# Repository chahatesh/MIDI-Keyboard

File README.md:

# MIDI Keyboard

This is a custom-built MIDI keyboard that I designed using a PCB and electronic components. The goal of this project was to create a compact, customizable MIDI controller with different types of inputs, including capacitive touch keys, buttons, sliders, and rotary encoders.

The keyboard is designed to be assembled by soldering components onto a custom PCB and uploading the firmware to the microcontroller.

All the PCB design files are included in this repository so you can build your own!

## Images

## Features

The MIDI keyboard includes several different controls:

- **Capacitive Touch Keys** – Touch-sensitive keys that can be used for musical notes or other inputs.
- **Push Buttons** – Additional buttons that can be programmed for different functions.
- **Sliders** – Adjustable controls for changing values such as volume or effects.
- **Rotary Encoders** – Rotating controls that can be used to adjust settings.
- **RGB LEDs** – SK6812MINI-E LEDs for visual feedback.
- **Custom PCB** – A board designed specifically for this project.

The firmware can be modified to change how the controls work, making the keyboard customizable for different applications.

## How to Build

### 1. Order the PCB

Start by downloading the PCB manufacturing files from this repository.

You can order the board from a PCB manufacturer such as [JLCPCB](https://jlcpcb.com/) or another PCB fabrication service.

Make sure to use the correct PCB files and check the board specifications before ordering.

### 2. Get the Components

Once you have ordered the PCB, you'll need to get all the electronic components required for the build.

These include the components shown in the PCB design, such as:

- Microcontroller and supporting components
- Buttons and switches
- Capacitive touch components
- Sliders
- Rotary encoders
- SK6812MINI-E LEDs
- Resistors, capacitors, and other components

Check the PCB design and bill of materials (BOM), if provided, for the exact parts and quantities.

### 3. Solder the Components

Once your PCB and components arrive, you can start assembling the keyboard.

Follow the PCB layout to determine where each component belongs.

I recommend starting with the smaller components before moving on to larger parts such as buttons, sliders, and rotary encoders.

Make sure that:

- Components are placed in the correct positions.
- Polarized components are facing the correct direction.
- Solder joints are clean and properly connected.
- There are no accidental solder bridges between pins.

Before connecting power, double-check the board for any mistakes.

### 4. Upload the Code

After soldering everything, connect the keyboard to your computer using the appropriate USB cable or programming connection.

Open the firmware in its supported development environment, select the correct board and port, and upload the code.

The firmware handles the keyboard's inputs and outputs, including its buttons, touch keys, sliders, encoders, and LEDs.

You can also modify the code to customize how the keyboard responds to different inputs.

### 5. Test Everything

After uploading the code, test the different parts of the keyboard.

Check that the buttons, touch keys, sliders, rotary encoders, and LEDs are responding correctly.

If something isn't working, check the solder joints, wiring, component orientation, and firmware settings.

If your firmware supports MIDI output, you can also connect the keyboard to compatible music software and test its MIDI controls.

### 6. Have Fun!

Once everything is working, your custom keyboard is ready!

You can experiment with different firmware, customize the controls, and use it for your own projects.

## CAD Design

The CAD model for this project is available on Onshape.

(https://cad.onshape.com/documents/587d2ace9f77041b4f50040f/w/845a50b27325c4e045b03186/e/2a77872a340160e4eacdba4f?renderMode=0&uiState=6ade809f7d59ddcf278d1ba7)

You can use this model to view the mechanical design, check dimensions, and understand how the parts fit together.

## Project Files

This repository contains the files needed to understand and reproduce the project.

- `Instrument/` – PCB design files, including the electronic design.
- `Images/` – Screenshots and images of the project.
- 'Code/' – Code used to control the keyboard, where included.

## Customization

One of the main reasons I made this keyboard was to have something that could be customized.

Depending on the firmware, you can experiment with different button functions, MIDI note mappings, slider controls, encoder behavior, and LED effects.

You can also modify the PCB design or CAD model to create your own version.

## About the Project

I created this project to learn more about PCB design, electronics, soldering, and programming.

It combines hardware and software into one device and provides a way to experiment with different input methods.

Feel free to explore the files, modify the design, and build your own version!

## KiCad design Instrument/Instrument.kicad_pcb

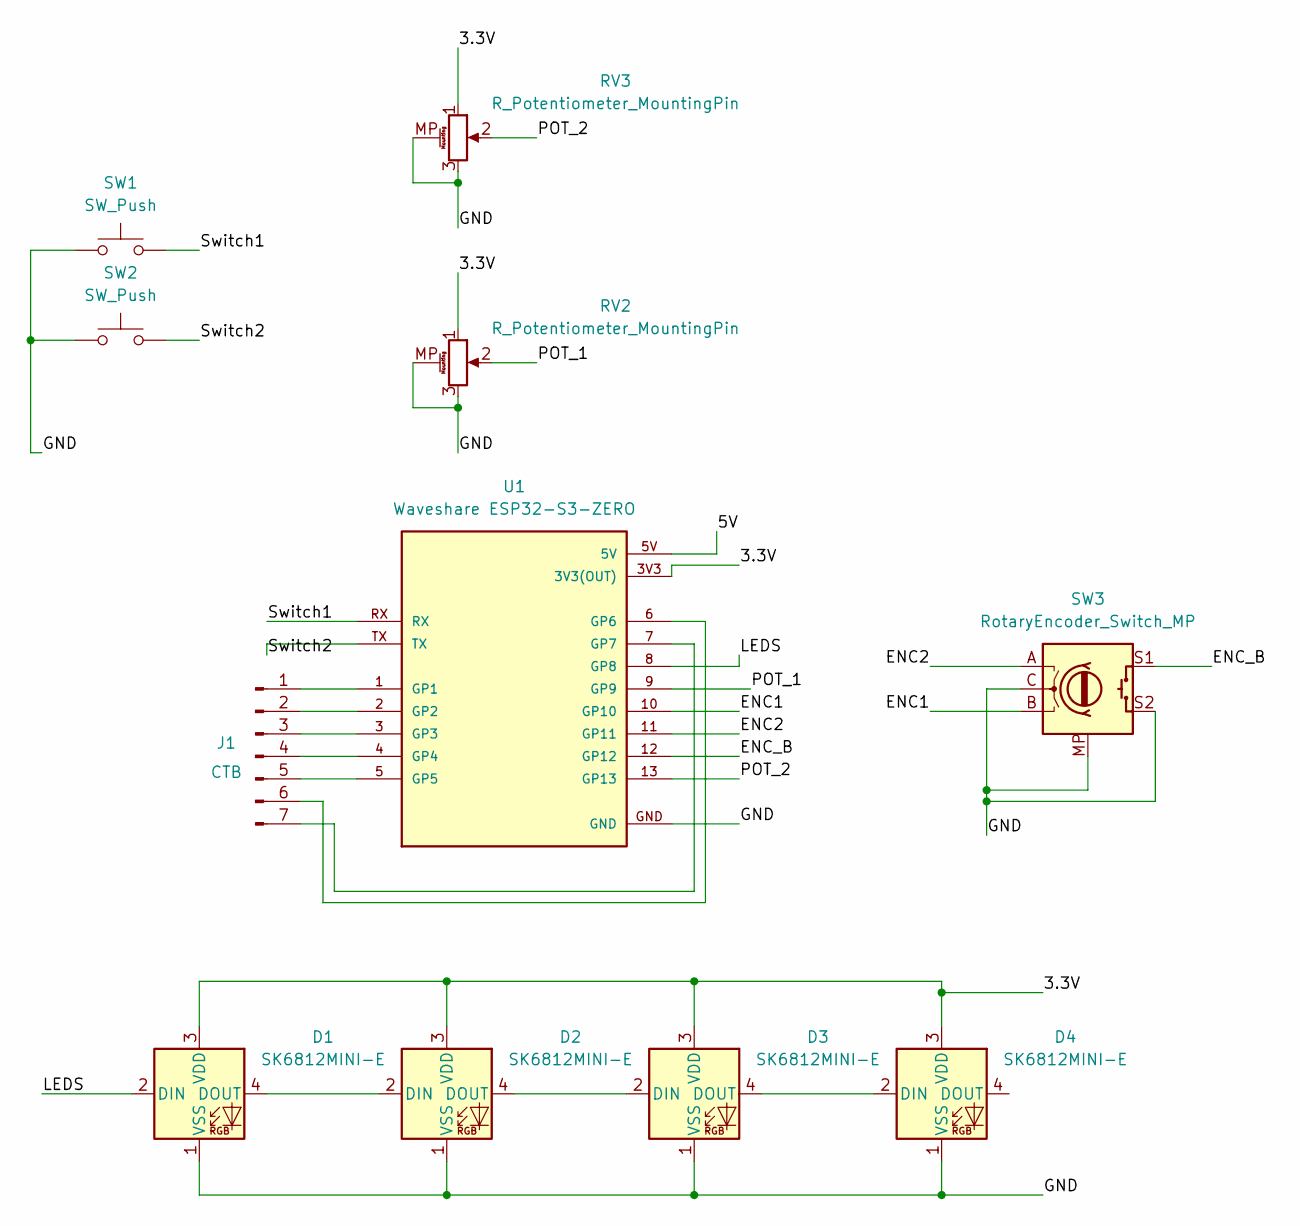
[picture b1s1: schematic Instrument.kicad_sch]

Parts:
D1, D2, D3, D4: SK6812MINI-E; LED_SK6812MINI-E_3.2x2.8mm_P1.5mm_ReverseMount
J1: CTB; Hex-Keys
RV2, RV3: R_Potentiometer_MountingPin; Potentiometer_Bourns_PTA1543_Single_Slide
SW1, SW2: SW_Push; Kailh Choc Low-Profile Switches
SW3: RotaryEncoder_Switch_MP; RotaryEncoder_Alps_EC11E-Switch_Vertical_H20mm_MountingHoles
U1: Waveshare ESP32-S3-ZERO; Waveshare ESP32-S3-Zero; PARTREV NA

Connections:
/3.3V: D1.3 (VDD), D2.3 (VDD), D3.3 (VDD), D4.3 (VDD), RV2.1, RV3.1, U1.3V3 (3V3(OUT))
/5V: U1.5V
/ENC1: SW3.B, U1.10 (GP10)
/ENC2: SW3.A, U1.11 (GP11)
/ENC_B: SW3.S1, U1.12 (GP12)
/GND: D1.1 (VSS), D2.1 (VSS), D3.1 (VSS), D4.1 (VSS), RV2.3, RV2.MP (MountPin), RV3.3, RV3.MP (MountPin), SW1.1, SW2.1, SW3.C, SW3.MP, SW3.S2, U1.GND
/LEDS: D1.2 (DIN), U1.8 (GP8)
/POT_1: RV2.2, U1.9 (GP9)
/POT_2: RV3.2, U1.13 (GP13)
/Switch1: SW1.2, U1.RX
/Switch2: SW2.2, U1.TX
unnamed: D1.4 (DOUT), D2.2 (DIN)
unnamed: D2.4 (DOUT), D3.2 (DIN)
unnamed: D3.4 (DOUT), D4.2 (DIN)
unnamed: J1.1, U1.1 (GP1)
unnamed: J1.2, U1.2 (GP2)
unnamed: J1.3, U1.3 (GP3)
unnamed: J1.4, U1.4 (GP4)
unnamed: J1.5, U1.5 (GP5)
unnamed: J1.6, U1.6 (GP6)
unnamed: J1.7, U1.7 (GP7)

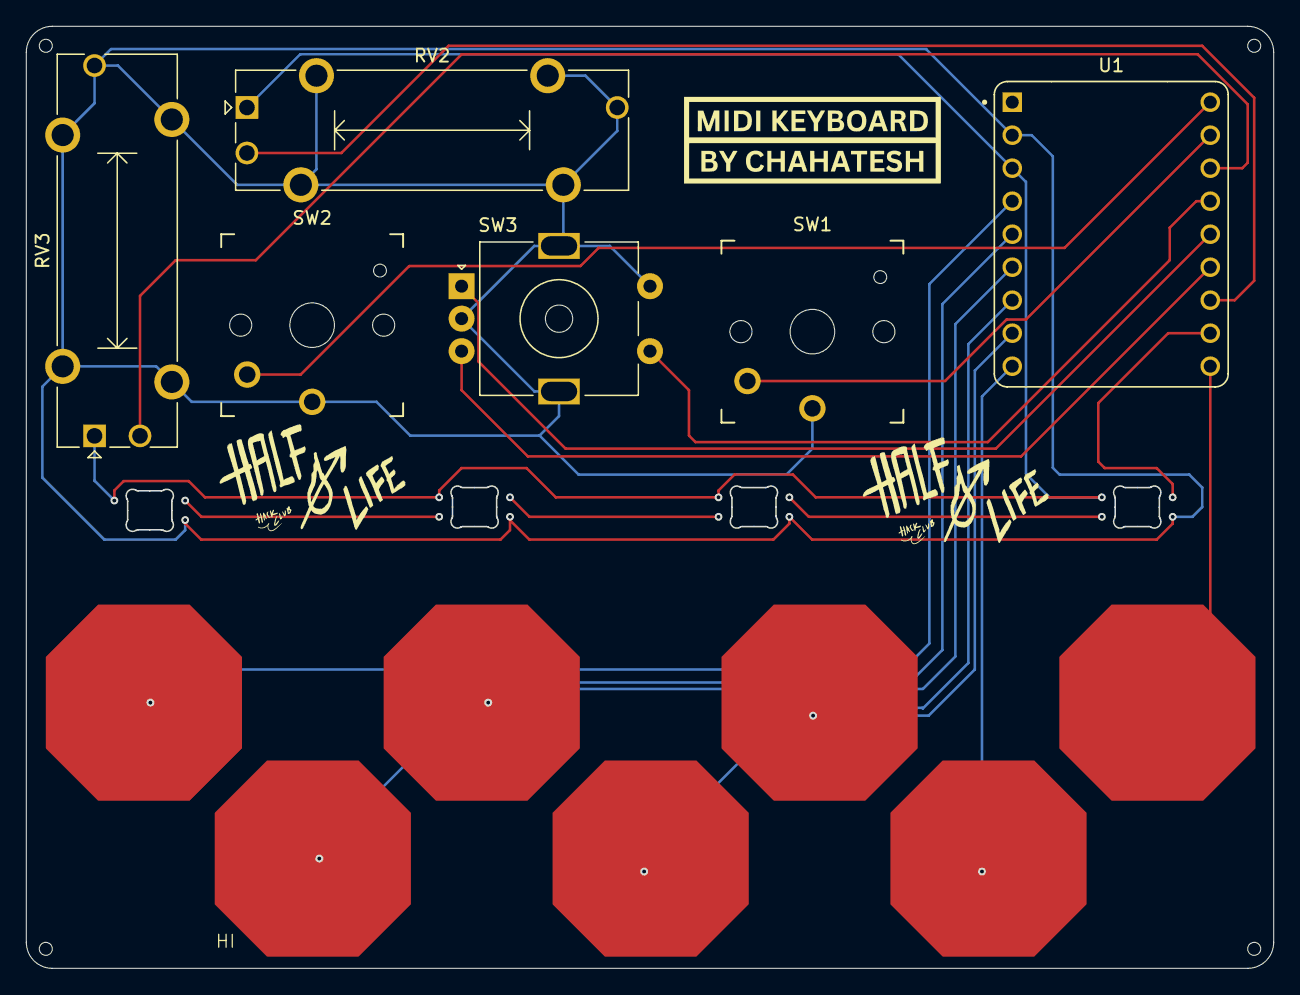
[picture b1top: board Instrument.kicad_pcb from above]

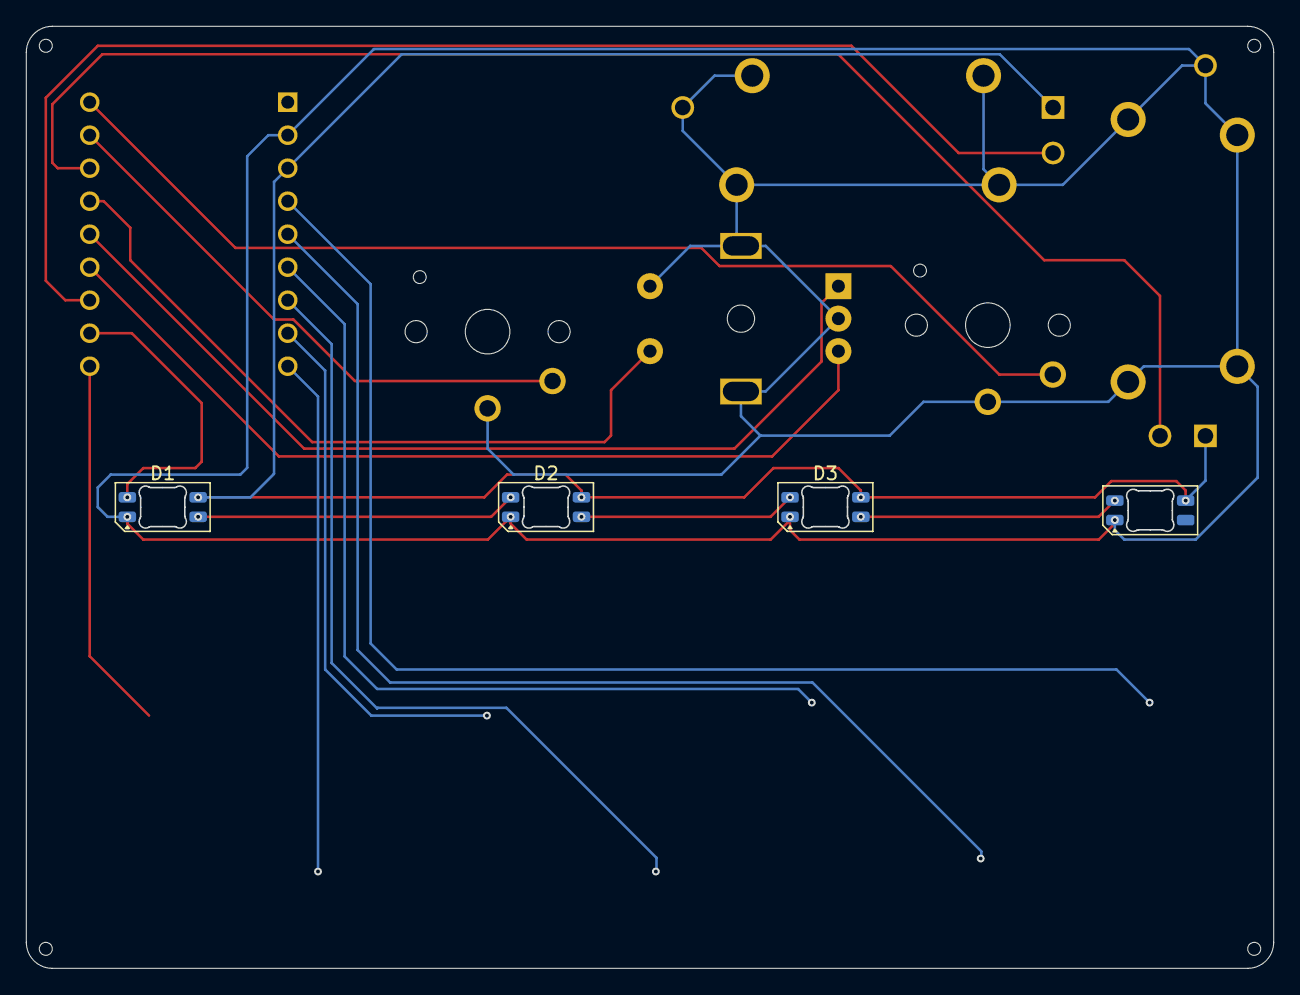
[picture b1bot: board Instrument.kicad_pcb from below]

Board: 2 copper layers, 96.0 x 72.5 mm, 11 parts (4 on the bottom side), 20 nets.

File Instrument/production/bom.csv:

Designator,Footprint,Quantity,Value,LCSC Part #
"D1, D2, D3, D4",LED_SK6812MINI-E_3.2x2.8mm_P1.5mm_ReverseMount,4,SK6812MINI-E,
J1,Hex-Keys,1,CTB,
"RV2, RV3",Potentiometer_Bourns_PTA1543_Single_Slide,2,R_Potentiometer_MountingPin,
"SW1, SW2",Kailh Choc Low-Profile Switches,2,SW_Push,
SW3,RotaryEncoder_Alps_EC11E-Switch_Vertical_H20mm_MountingHoles,1,RotaryEncoder_Switch_MP,
U1,Waveshare ESP32-S3-Zero,1,Waveshare ESP32-S3-ZERO,
